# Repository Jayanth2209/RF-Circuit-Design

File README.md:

# RF Circuit Design
#### [Link to the Video](https://youtu.be/TnRn3Kn_aXg)         

### Five Rules: 
#### 1) Use 4 Layers:      
* Top (RF and Signals)          
* GND just below 1                 
* VCC above the bottom (15 on Eagle)           
* Bottom (Signals)             

* Use a consistent stack-up            
* Dedicate entire inner layers to unbroken power supply planes           
* Keep RF Signals on Top     

##### 4-Layer Board stackup:   
The 4 layer board stackup is as follows:      
* 1 mil solder resist      
* 1 oz Cu (1.4 mil)    
* 6.7 mil prepreg     
* 0.5 oz Cu (0.7 mil)   
* 47 mil Core     
* 0.5 oz Cu (0.7 mil)           
* 6.7 mil prepreg        
* 1 oz Cu (1.4 mil)         
* 1 mil solder resist         

[Setting up Multi-layer on Eagle](https://youtu.be/0sVUkjXbqrM)            

#### 2) Choose Integrated components:     
Try to choose and use the most integrated components - RF ICs, Baluns, Filters, etc.     
Examples of RF ICs - CC2650, CC1310, AT86RF215, nRF24L01P(+) ans so many more integrated RF ICs are available...        

#### 3) 50 Ohms everywhere:     
Try to match everything to 50 ohms. If a component is not 50 ohms I/O or whatever, convert it to 50 ohms.     
How? - Refer to it's Datasheet (Matching/Application Circuit)    

* Follow Manufacturer Recommendations (for matching)  -------------  **(4)**      

##### Note: For matching the RF traces on the Top layer of the circuit board to 50 Ohms, they have to be 12 mils wide (Considering the 4 layer board stackup specifications as mentioned above). So, on Eagle, Set - Trace width = 12 mils, Trace thickness = 1.4 mils             

After making your circuit, with all the above rules in mind:       
* Route RF first  --------------  **(5)**    
* Keep RF traces short and direct     
* Keep other signals away from RF (keep buffer zones next to RF traces, try to route other signals considerable away from RF signals)

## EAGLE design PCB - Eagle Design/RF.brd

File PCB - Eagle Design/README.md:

# PCB        
A PCB has been designed on Eagle with the following components:           
[Reference Schematic]()          

* RF Transceiver:      
CC1121 - Texas Instruments        
[Datasheet - CC1121](https://www.ti.com/lit/ds/swrs111f/swrs111f.pdf?ts=1603287573940&ref_url=https%253A%252F%252Fwww.google.com%252F)       

* Antenna:     
ANT-916-CW-RCL-CCC      
[Antenna Datasheet]()       

* Other Components(Crystal Oscillator, Capacitors, Resistors and Inductors)       
[Components List]()      

* RF Module with Type-C USB Connector: Designed using Eagle       
[RF Module 1]()        
This module can be independently powered via a type-C USB connector or it can also be interfaced with an MCU(includes VCC, GND, GPIOs and pins corresponding to SPI Interfacing of the module)     

* RF Module without Type-C connector: Designed using Eagle      
[RF Module 2]()       
Only for interfacing with MCUs       
 
### PCB Design Guidelines:
Refer to these for important things to note while designing a PCB:     
[General guidelines for desiging an aesthetically pleasing PCB]()             
[RF PCB Design - A few things to note]()          

### Comparing the various types of Commercially available antennas:         

### Increasing the range of an RF-Module and theoretical Range estimations:           

### Calculating the range of the above designed PCB (CC1121 RF Transceiver):

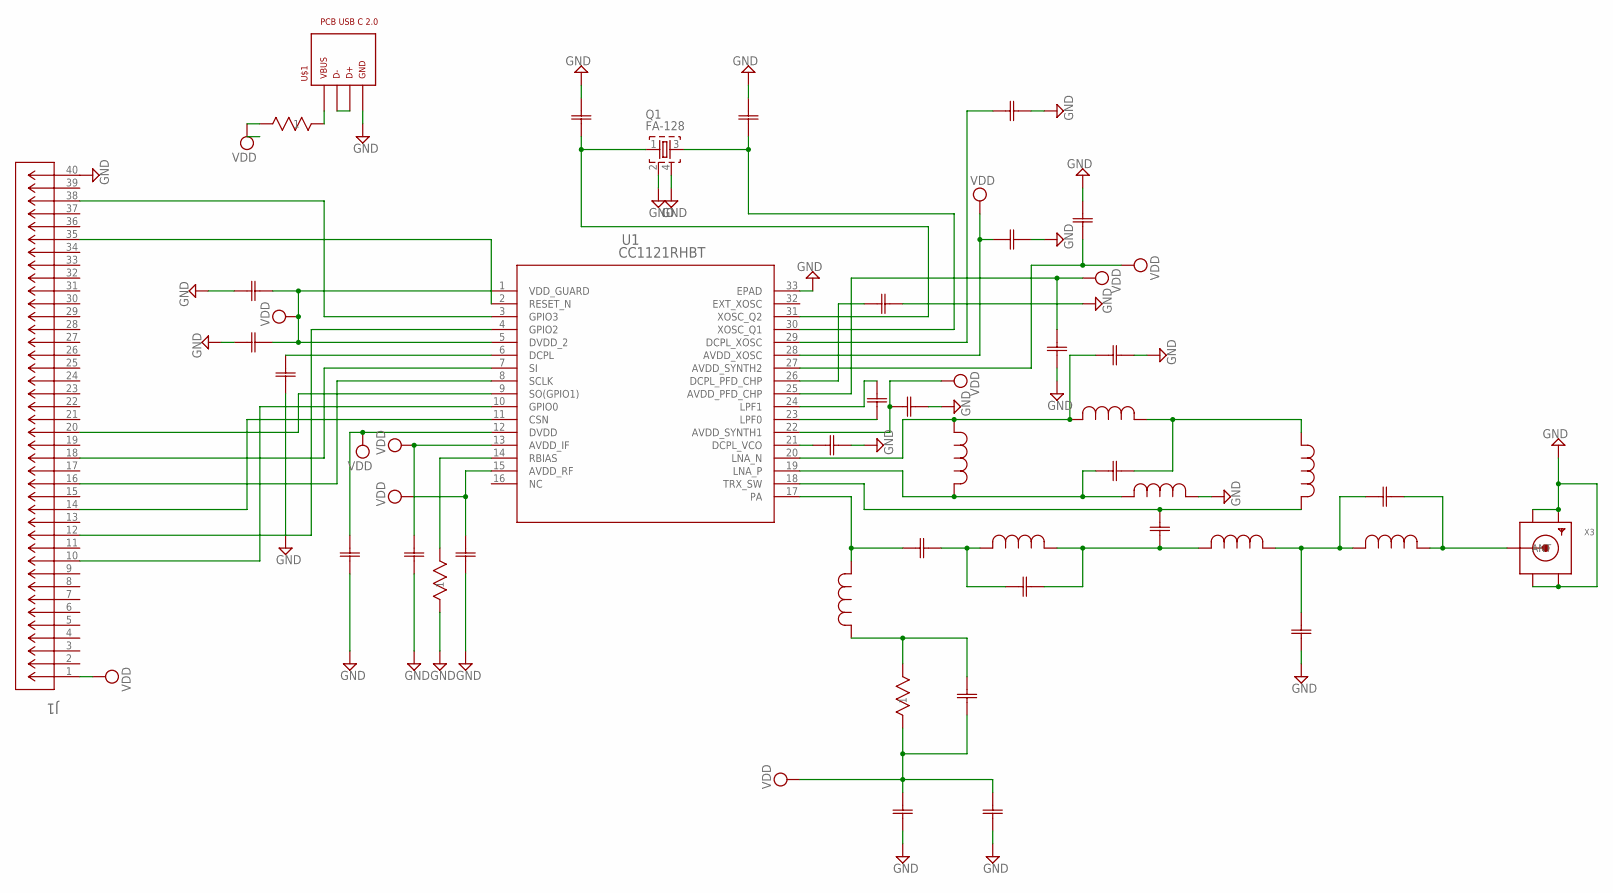
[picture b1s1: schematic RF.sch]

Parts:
C1, C9: 220nF; G-155_MUR
C2, C6, C7, C8, C20, C21, C22, C23, C26: 47nF; G-155_MUR
C3, C24, C25: 15pF; G-155_MUR
C4: 1pF; G-155_MUR
C5: 2.2pF; G-155_MUR
C10: 33pF; G-155_MUR
C11, C12: 10pF; G-155_MUR
C13: 3pF; G-155_MUR
C14: GRM155R71A104KA01D; G-155_MUR
C15, C16: 3.3pF; G-155_MUR
C17, C18: 10nF; G-155_MUR
C19: 1.8nF; G-155_MUR
J1: CLT-110-02-L-D-BE; CON20_2X10_DUME_CLT_SAI
L1, L2, L3: 10nH; IND_LQW15AN13NG00D_MUR
L4, L6, L7, L8: 12nH; IND_LQW15AN13NG00D_MUR
L5: 15nH; IND_LQW15AN13NG00D_MUR
Q1: FA-128
R1, R2, R3: 56k; RES_1E0402_1XP5_KOA
U1: CC1121RHBT; RHB32_3P45X3P45_TEX
U$1: PCB_USB_C_2.0DS_1; USB_TYPE_C_DS_1
X3: SMACONNECTOR_EDGE; SMA_EDGELAUNCH

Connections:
GND: C1.1, C2.1, C6.1, C7.1, C8.1, C9.1, C11.1, C12.1, C13.1, C16.2, C17.2, C18.2, C20.1, C21.2, C22.2, C23.2, C24.2, C25.2, C26.2, J1.40, L8.1, Q1.2, Q1.4, R1.1, U1.33 (EPAD), U$1.A1 (GND), U$1.A12 (GND), U$1.B1 (GND), U$1.B12 (GND), X3.GND@1 (GND4), X3.GND@2 (GND3), X3.GND@3 (GND2), X3.GND@4 (GND1)
unnamed: J1.35, U1.2 (RESET_N)
unnamed: J1.38, U1.3 (GPIO3)
unnamed: J1.12, U1.4 (GPIO2)
unnamed: C9.2, U1.6 (DCPL)
unnamed: J1.18, U1.7 (SI)
unnamed: J1.16, U1.8 (SCLK)
unnamed: J1.20, U1.9 (SO(GPIO1))
unnamed: J1.10, U1.10 (GPIO0)
unnamed: J1.14, U1.11 (CSN)
unnamed: R1.2, U1.14 (RBIAS)
unnamed: C3.1, L1.1, U1.17 (PA)
unnamed: C3.2, C4.1, L2.2
unnamed: C5.2, L7.1, U1.18 (TRX_SW)
unnamed: C4.2, C5.1, L2.1, L3.2
unnamed: C10.2, L1.2, R2.2
unnamed: C15.2, L6.1, L7.2
unnamed: C13.2, C14.1, L3.1, L4.2
unnamed: C17.1, U1.21 (DCPL_VCO)
unnamed: C14.2, L4.1, X3.P (ANT)
unnamed: C15.1, L5.1, L8.2, U1.19 (LNA_P)
unnamed: C16.1, L5.2, L6.2, U1.20 (LNA_N)
unnamed: C19.1, U1.23 (LPF0)
unnamed: C19.2, U1.24 (LPF1)
unnamed: C26.1, U1.29 (DCPL_XOSC)
unnamed: C21.1, U1.26 (DCPL_PFD_CHP)
unnamed: C25.1, Q1.3, U1.30 (XOSC_Q1)
unnamed: C24.1, Q1.1, U1.31 (XOSC_Q2)
unnamed: R3.1, U$1.A4 (VBUS), U$1.A9 (VBUS), U$1.B4 (VBUS), U$1.B9 (VBUS)
unnamed: U$1.A6 (D+), U$1.A7 (D-), U$1.B6 (D+), U$1.B7 (D-)
VDD: C1.2, C2.2, C6.2, C7.2, C8.2, C10.1, C11.2, C12.2, C18.1, C20.2, C22.1, C23.1, J1.1, R2.1, R3.2, U1.1 (VDD_GUARD), U1.5 (DVDD_2), U1.12 (DVDD), U1.13 (AVDD_IF), U1.15 (AVDD_RF), U1.22 (AVDD_SYNTH1), U1.25 (AVDD_PFD_CHP), U1.27 (AVDD_SYNTH2), U1.28 (AVDD_XOSC)

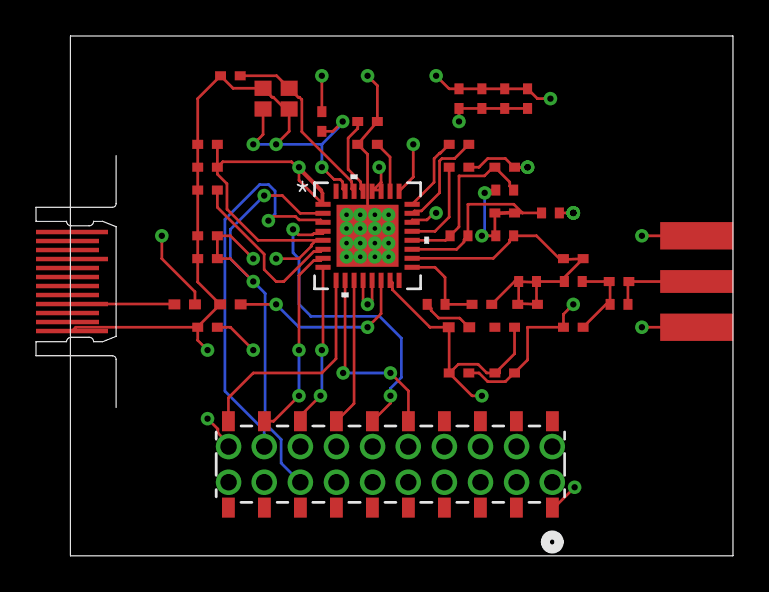
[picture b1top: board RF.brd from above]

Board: 4 copper layers, 38.7 x 28.9 mm, 42 parts (0 on the bottom side), 31 nets.

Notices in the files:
parts and their libraries:
COPYRIGHT: Copyright (C) 2015 Accelerated Designs. All rights reserved
COPYRIGHT: Copyright (C) 2018 Accelerated Designs. All rights reserved
